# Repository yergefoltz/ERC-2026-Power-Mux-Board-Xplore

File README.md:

# ERC-2026-Power-Mux-Board-Xplore
This is the first version of this power mux board uses LTC4421 as a "brain".
It takes measurements, switched between power sources accordingly to their priority of quality.

The LTC4421 measures each channel’s current from the voltage across its 0.4 mΩ shunt (ΔV_SNS = I · R_SENSE), sensed through Kelvin connections. It uses this voltage for three things:

Current limiting. When ΔV_SNS reaches 25 mV (20–30 mV over tolerance), the controller reduces the MOSFET gate voltage so the current stays at I_LIM = 25 mV / 0.4 mΩ ≈ 62.5 A (50–75 A).
Overcurrent fault timing. While the channel is in current limit, the TMR capacitor charges. If the overcurrent lasts longer than t_TMR, the channel is turned off and flags FAULT.
Fast short-circuit response. If ΔV_SNS exceeds 50 mV (≈125 A), the gate is pulled down with 50 mA so the current is brought back under control within microseconds.

The TVS diodes protect the board from fast voltage transients. D7 and D8 sit on the inputs (cable and battery), D9 on the output.

In normal operation they do not conduct: below V_RWM = 33 V the leakage is only µA, and the maximum battery voltage is 29.4 V.
During a spike they break down (V_BR ≥ 36.7 V) and clamp the voltage, sending the surge current to ground. Typical spikes are:
inductive kicks when a cable is hot-plugged (cable inductance ringing with the ceramic capacitors);
motor regeneration and inductive kicks;
ESD.
Coordination with the LTC4421: V_BR,min (36.7 V) is above the LTC4421 OV threshold (34.9 V). Sustained overvoltage is therefore handled by the controller, which disconnects the source. The TVS only absorbs short transients (rated 1500 W for a 10/1000 µs pulse).
Reverse polarity: a unidirectional TVS conducts in the forward direction and acts as a crowbar, so the fuse opens.

Fuses (F1, F2 – MAXI 40 A)

The fuses protect against board failures, not against output short circuits.

Output shorts are handled by the LTC4421. It limits the current to ≤ 75 A for ≤ 1.25 ms: I²t ≈ 75² × 1.25 ms ≈ 7 A²s, which is negligible for a 40 A fuse.
The fuse opens when the controller cannot limit the current:
a shorted MOSFET;
a shorted TVS or input capacitor;
reverse polarity (TVS crowbar);
a wiring short before the controller.
In these cases the battery can deliver hundreds of amps, and the fuse clears in a fraction of a second.
Normal load: the 40 A / 2 s peak is 1× the rated current, so the fuse does not blow. MAXI fuses are rated 32 V DC, above the 29.4 V maximum.
Timers: TMR and QUAL

TMR – overcurrent fault timer (C10/C11 = 10 nF)

While a channel is in current limit, the TMR capacitor charges at 6 µA.
After t_TMR = 83 µs/nF × 10 nF ≈ 0.83 ms (0.55–1.25 ms), the channel turns off and FAULT is asserted.
A cool-down of 1024 × t_TMR (≈ 0.85 s) follows. Because FAULT is tied to DISABLE, the channel then retries automatically.
Lower bound: t_TMR must be longer than the time needed to charge the output capacitance at start-up:
t_TMR,min > 1.5 × C_OUT · V_IN / (I_LIM − I_LOAD)
Upper bound: the MOSFET SOA, since the MOSFET dissipates about V_IN × I_LIM for the whole t_TMR.

QUAL – input qualification timer (C9 = 3.3 nF)

A source must stay inside its valid UV/OV window continuously for t_VALID = 16 ms/nF × 3.3 nF ≈ 53 ms before it can be connected.
This rejects contact bounce while the XT60 connector is being inserted, as well as noise and short glitches.
Connecting is deliberately slow (53 ms). Disconnecting is fast (t_INVALID ≤ 8 µs).

Board logic
Two sources:
Channel 1 = 28 V cable PSU (priority);
Channel 2 = 7S Li-ion battery (21–29.4 V).
Each path goes through a fuse, TVS, input capacitor, a back-to-back N-MOSFET pair with a sense resistor, and then to the common output.

Input monitoring: a resistor divider per input sets three thresholds.
Source	UV rising	UV falling	OV
Cable	24.85 V		23.87 V		34.9 V
Battery	24.05 V		21.0 V		35.0 V

Priority: whenever the cable is valid, the output is fed from the cable and the battery is disconnected. Otherwise the battery feeds the output.

Switchover:
When the cable is unplugged or sags below its falling threshold, the cable channel turns off within ≤ 8 µs.
After a break-before-make time of ≤ 15 µs, the battery channel turns on.
The 220 µF output capacitor C6 holds the bus meanwhile, with a droop of about 2 V at 20 A.
When the cable returns and qualifies for 53 ms, the board switches back.
Back-to-back MOSFETs block current in both directions. The battery can never back-feed the PSU, and the two sources are never connected together.

Protection:
current limit with fault timer and auto-retry;
UV/OV lockout;
fast gate pull-down above 50 mV;
current-limit foldback (halved) when the output is hard-shorted (< 0.41 V);
TVS for transients;
fuses for catastrophic failures.
User interface:
LEDs show which inputs are valid and which channel is active;
the SHDN connector (J4) turns both channels off.

Start-up:
the charge-pump reservoir capacitor C5 (2.2 µF) charges first (~0.5 s);
the inputs are then qualified;
the highest-priority valid source is connected.

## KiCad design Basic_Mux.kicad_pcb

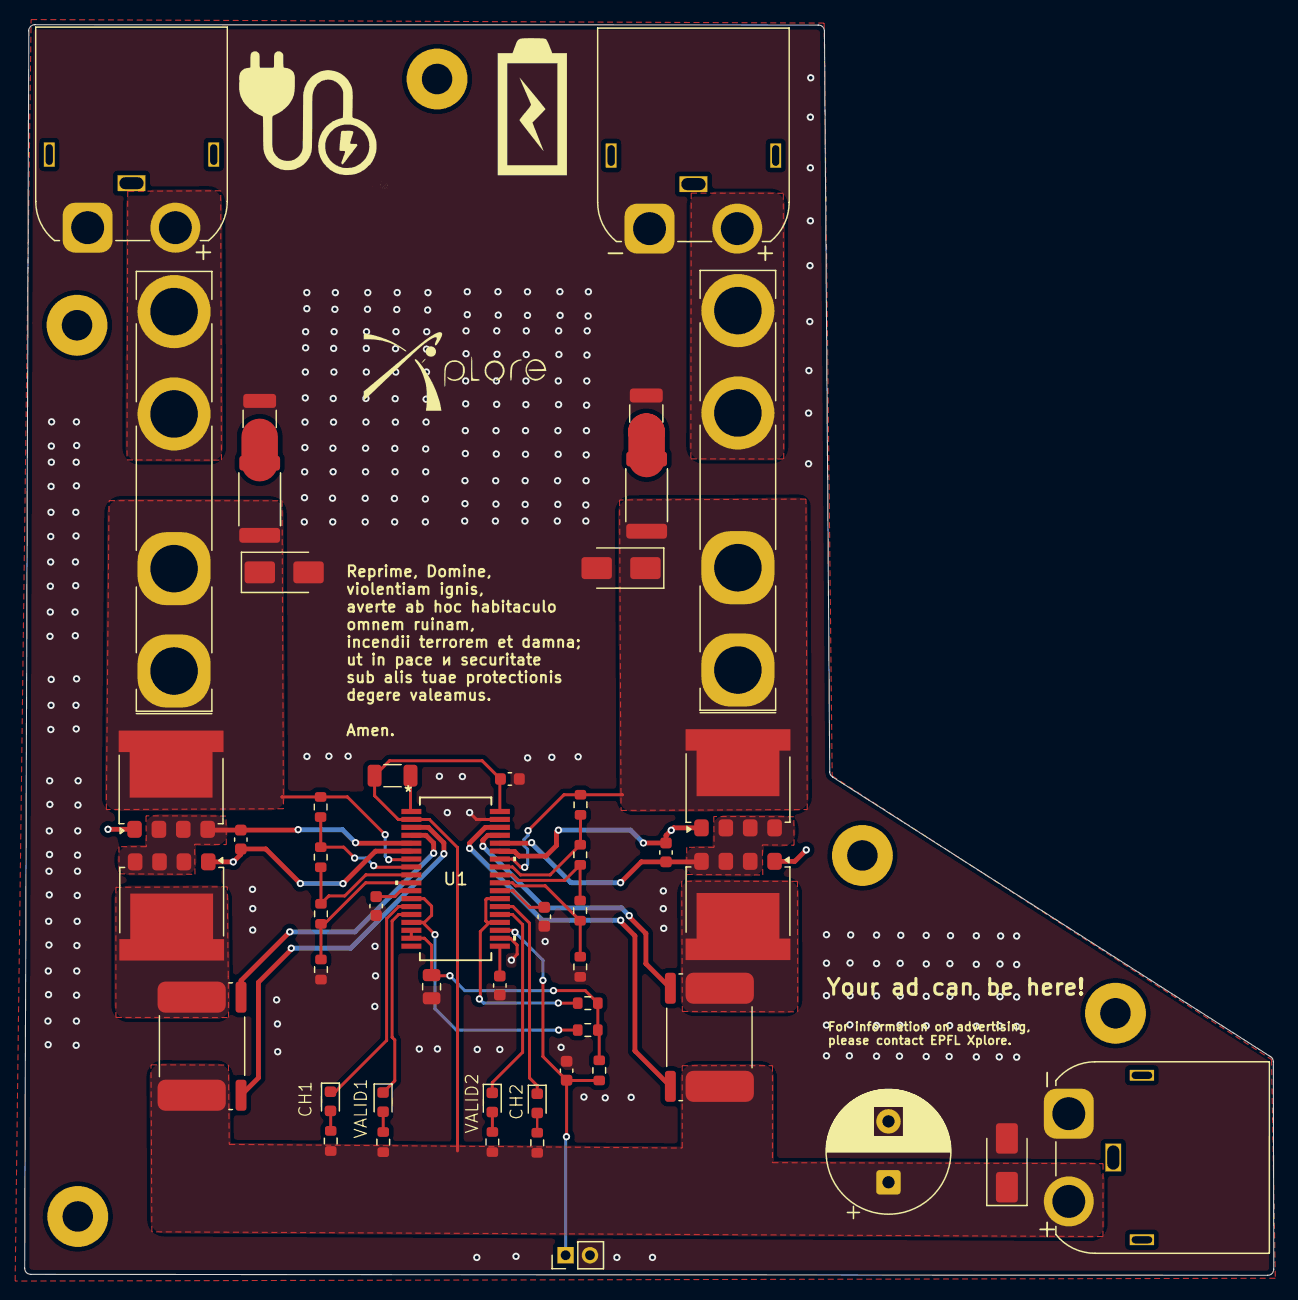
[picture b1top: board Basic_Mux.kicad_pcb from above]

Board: 4 copper layers, 102.5 x 102.6 mm, 54 parts (0 on the bottom side), 40 nets.

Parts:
C1, C2: 10uF; C_1210_3225Metric
C4, C7: 47nF; C_0603_1608Metric
C5: 2.2uF; C_1206_3216Metric
C6: 220uF; CP_Radial_D10.0mm_P5.00mm
C8: 0.1uF; C_0603_1608Metric
C9: 3.3nF; C_0603_1608Metric
C10, C11: 10nF; C_0603_1608Metric
C12: 2.7uF; C_0805_2012Metric
C13: 100nF; C_0603_1608Metric
D1, D3, D4, D6: LED; LED_0603_1608Metric
D7, D8, D9: SMCJ33A; D_SMA
F1, F2: 40A; Fuseholder_Keystone_3555-2
H7, H9, H10, H11, H12: MountingHole_Pad; MountingHole_2.5mm_Pad
J1, J2: XT60PW_M; AMASS_XT60IPW-M_1x03_P7.20mm_Horizontal
J3: XT60PW_F; AMASS_XT60IPW-M_1x03_P7.20mm_Horizontal
J4: Conn_01x02; PinHeader_1x02_P2.00mm_Vertical
Q1, Q2, Q3, Q4: SQJQ184E; LFPAK88
R1, R2: 0.47; R_2512_6332Metric
R3, R4: 0.4m; R_Shunt_Isabellenhuette_BVR4026
R5, R9: 976k; R_0603_1608Metric
R6: 825; R_0603_1608Metric
R7: 5.76k; R_0603_1608Metric
R8, R12: 14.3k; R_0603_1608Metric
R10: 3.01k; R_0603_1608Metric
R11: 6.49k; R_0603_1608Metric
R13, R14, R16, R17: 27k; R_0603_1608Metric
R15, R18, R19: 100k; R_0603_1608Metric
U1: LTC4421CG-PBF; G_05-08-1640_ADI

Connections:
+V_Cable: D7.1 (A1), F2.1, Q3.5 (D), R1.2, R5.1, U1.7 (V1)
+V_battery: D8.1 (A1), F1.1, Q4.5 (D), R2.2, R9.1, U1.30 (V2)
+V_output: C5.1, C6.1, C8.2, D9.1 (A1), J3.2, R3.4, R4.1, R13.2, R14.2, R16.2, R17.2, U1.2 (CPOREF), U1.36 (EXTVCC)
/LTC_controller/CH1: D6.1 (K), U1.13 (*CH1)
/LTC_controller/CH2: D3.1 (K), U1.24 (*CH2)
/LTC_controller/CPO: C5.2, U1.1 (CPO)
/LTC_controller/Gate1: C4.1, Q1.1 (G), Q3.1 (G), U1.6 (GATE1)
/LTC_controller/Gate2: C7.1, Q2.1 (G), Q4.1 (G), U1.31 (GATE2)
/LTC_controller/OV1: R7.2, R8.1, U1.10 (OV1)
/LTC_controller/OV2: R11.2, R12.1, U1.27 (OV2)
/LTC_controller/Out1: R4.2, U1.3 (OUT1)
/LTC_controller/Out2: R3.3, U1.34 (OUT2)
/LTC_controller/Sense1: R4.3, U1.4 (SENSE1)
/LTC_controller/Sense2: R3.2, U1.33 (SENSE2)
/LTC_controller/Source2: C7.2, Q2.2 (S), Q2.3 (S), Q2.4 (S), Q4.2 (S), Q4.3 (S), Q4.4 (S), U1.32 (SOURCE2)
/LTC_controller/TO_INT: C12.2, R15.2, R18.1, R19.2, U1.16 (CASIN), U1.17 (INTVCC)
/LTC_controller/UVF1: R5.2, R6.1, U1.8 (UVF1)
/LTC_controller/UVF2: R9.2, R10.1, U1.29 (UVF2)
/LTC_controller/UVR1: R6.2, R7.1, U1.9 (UVR1)
/LTC_controller/UVR2: R10.2, R11.1, U1.28 (UVR2)
/LTC_controller/VALID1: D1.1 (K), U1.14 (*VALID1)
/LTC_controller/VALID2: D4.1 (K), U1.23 (*VALID2)
GND: C1.1, C2.1, C6.2, C8.1, C9.1, C10.1, C11.1, C12.1, C13.1, D7.2 (A2), D8.2 (A2), D9.2 (A2), J1.1, J2.1, J3.1, J4.2, R8.2, R12.2, U1.20 (RETRY), U1.35 (GND)
unnamed: C1.2, R1.1
unnamed: C2.2, R2.1
unnamed: D1.2 (A), R14.1
unnamed: D3.2 (A), R16.1
unnamed: D4.2 (A), R17.1
unnamed: D6.2 (A), R13.1
unnamed: F2.2, J1.2
unnamed: F1.2, J2.2
unnamed: C13.2, J4.1, R19.1, U1.21 (*SHDN)
unnamed: Q1.5 (D), R4.4
unnamed: Q2.5 (D), R3.1
unnamed: R18.2, U1.12 (*DISABLE1), U1.15 (*FAULT1)
unnamed: R15.1, U1.22 (*FAULT2), U1.25 (*DISABLE2)
unnamed: C9.2, U1.19 (QUAL)
unnamed: C4.2, Q1.2 (S), Q1.3 (S), Q1.4 (S), Q3.2 (S), Q3.3 (S), Q3.4 (S), U1.5 (SOURCE1)
unnamed: C11.2, U1.11 (TMR1)
unnamed: C10.2, U1.26 (TMR2)
